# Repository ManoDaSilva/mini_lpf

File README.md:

# Mini LPF: an HF low pass filter kit

A small low pass filter (LPF) for QRP transmitters on the HF amateur bands, from 80m to 10m. It has SMA connectors on both ends and three hand-wound toroidal inductors.

This is an entry-level project. The aim is to learn how a low pass filter works and how to design and wind a toroidal inductor. You choose your band, wind three coils and solder four capacitors. The result is a working harmonic filter you can put after any small transmitter, such as an Si5351 beacon or a QRP PA.

## Context

The kit was designed for a YOTA (Youngsters On The Air) sub-regional event, with 30 kits to build in a workshop. YOTA is the youth programme of IARU Region 1 ([ham-yota.com](https://www.ham-yota.com/), [IARU R1 Youth](https://www.iaru-r1.org/about-us/committees-and-working-groups/youth/)).

The design goals for the event were:

- Low cost: under 2 EUR per participant if possible.
- Few different parts: one core type and one wire size for every band.
- SMA input and output, on a custom PCB.
- A choice of band for each participant: 80m, 40m, 20m, 15m or 10m.

The design is not limited to the event. Anyone who needs a small harmonic filter or wants to learn about filters can use it. The table below covers all HF bands from 80m to 10m.

## Repository content

| Folder | Content |
|---|---|
| `mini_lpf_pcb/` | KiCad project: schematic, PCB and footprints |
| `docs/` | Source documentation, including the original G-QRP filter article (`gqrplpf.pdf`) |

## Working principle

A transmitter does not only put out its wanted frequency. It also puts out harmonics: signals at 2, 3, 4 or more times that frequency. A square-wave source, such as an Si5351 or a switching PA, is rich in odd harmonics. These harmonics can cause interference on other bands, and radio rules require them to be kept low.

A low pass filter lets frequencies below its cutoff pass with little loss and attenuates frequencies above it. This filter is a 7-element Chebyshev design by Ed Wetherhold, W3NQN. George Dobbs, G3RJV, published a practical version for the G-QRP Club (see `docs/gqrplpf.pdf`). It uses standard capacitor values, which makes it easy to build.

```
IN o----+---L1---+---L2---+---L3---+----o OUT
        |        |        |        |
        C1       C2       C3       C4
        |        |        |        |
       GND      GND      GND      GND
```

The filter has 50 ohm input and output impedance and is symmetrical, so IN and OUT can be swapped.

Component numbering in this repo follows the signal path: C1, L1, C2, L2, C3, L3, C4. The G-QRP article numbers the parts 1 to 7 along the ladder. The mapping is:

| This repo | G-QRP article |
|---|---|
| C1, C4 | C1, C7 |
| C2, C3 | C3, C5 |
| L1, L3 | L2, L6 |
| L2 | L4 |

## Band values (80m to 10m)

All coils are wound on a T37-6 (yellow) core. Capacitor values are in pF. Inductance values come from Table 1 of the G-QRP article, except 60m, which comes from the QRP Labs LPF kit (the G-QRP article has no 60m filter).

| Band | Cutoff F-co (MHz) | -3 dB (MHz) | C1, C4 (pF) | C2, C3 (pF) | L1, L3 (µH) | L1, L3 turns | L2 (µH) | L2 turns |
|---|---|---|---|---|---|---|---|---|
| 80m | 4.125 | 5.11 | 470 | 1200 | 2.434 | 28 | 3.012 | 32 |
| 60m | | | 680 | 1200 | 2.12 | 27 | 2.30 | 28 |
| 40m | 7.36 | 9.04 | 270 | 680 | 1.380 | 21 | 1.698 | 24 |
| 30m | 10.37 | 11.62 | 270 | 560 | 1.090 | 19 | 1.257 | 20 |
| 20m | 14.40 | 16.41 | 180 | 390 | 0.773 | 16 | 0.904 | 17 |
| 17m | 18.93 | 22.89 | 110 | 270 | 0.548 | 13 | 0.668 | 15 |
| 15m | 21.55 | 27.62 | 82 | 220 | 0.444 | 12 | 0.561 | 14 |
| 12m | 25.24 | 28.94 | 100 | 220 | 0.438 | 12 | 0.515 | 13 |
| 10m | 31.66 | 40.52 | 56 | 150 | 0.303 | 10 | 0.382 | 11 |

Notes on the table:

- The G-QRP article winds 80m on a T37-2 (red) core with 25 and 27 turns. This repo uses T37-6 on every band so that the kit needs only one core type. On T37-6, 80m needs 28 and 32 turns.
- For 40m, Table 4 of the G-QRP article lists 19 and 21 turns on T37-6. The turns formula with the Table 1 inductances gives 21 and 24 turns. The QRP Labs kit also uses 21 and 24 turns on T37-6 for 40m. This repo uses 21 and 24.
- For 17m, the G-QRP value for C1 and C4 is 110 pF. QRP Labs uses 100 pF because 110 pF is hard to find. 100 pF and 10 pF in parallel give 110 pF.
- For 80m and 60m, 1200 pF can be made from 1000 pF and 220 pF in parallel (1220 pF), or 680 pF and 470 pF (1150 pF).

## Designing a coil yourself

The number of turns comes from the inductance and the core's AL value:

```
N = 10 x sqrt(L / L10)
```

- N is the number of turns.
- L is the inductance you need, in µH.
- L10 is the inductance of the core with 10 turns, in µH. For a T37-6 it is 0.30 µH. For a T37-2 it is 0.40 µH.

Example for the 20m L1: N = 10 x sqrt(0.773 / 0.30) = 16.05, so 16 turns.

Round to the nearest whole number of turns. The AL value of the core has a tolerance of about 5%, so the result does not need to be more precise than that.

The same formula works with the AL value given in nH per turn squared: N = sqrt(L / AL). For a T37-6, AL is 3.0 nH/turn².

## Recommended components

| Qty | Part | Notes |
|---|---|---|
| 3 | T37-6 iron powder toroid (yellow) | Micrometals or Amidon. Unbranded cores may use a different mix. Measure a sample before you buy many. |
| 1.5 m | Enamelled copper wire, 0.35 to 0.4 mm (AWG 27 to 26) | Use solderable (polyurethane) enamel, which strips with a hot soldering iron. |
| 4 to 8 | Ceramic disc capacitors, C0G / NP0 | Values from the table. 5.08 mm lead spacing. 50 V or more, 100 V if you use more than 5 W. |
| 2 | SMA female, edge-mount | Made for a 1.6 mm board. Check the footprint against the exact part you buy. |
| 1 | PCB from `mini_lpf_pcb/` | 2 layers, 1.6 mm FR4 |

Why T37-6: Micrometals mix 6 is made for about 3 to 40 MHz, which covers all bands from 80m to 10m. The G-QRP article (Table 3) rates the T37-6 for up to 25 W.

Why 0.4 mm wire: the hardest coil is the 80m L2 with 32 turns. With enamel, 0.4 mm wire is about 0.45 mm thick. 32 turns take about 14.4 mm of the 15 mm available at the inner edge of the core. It fits in one layer, but only just. 0.35 mm wire leaves more room. On the higher bands the wire size does not matter, because the coils have far fewer turns.

### About capacitors

C0G (also sold as NP0) capacitors are the right choice. Their value stays stable with temperature and voltage, and their RF loss is low.

Generic ceramic discs without a temperature rating can work, with some care:

- Avoid Z5U and Y5V types. Their value can drop by half when cold, which moves the cutoff up so far that the 2nd harmonic is barely attenuated.
- Y5P and X7R types are acceptable. They add about 0.5 dB of loss, which does not matter at QRP power.
- Buy each value from one batch. When all capacitors are off in the same direction, the filter stays matched. When some are high and some are low, the match gets poor (return loss of 5 to 8 dB).
- Small values (100 pF and below) are usually class 1 ceramics anyway, even when sold as generic.
- If you can, measure a few capacitors of each batch with a component tester.

## Winding the toroids

- Each time the wire passes through the centre of the core counts as one turn. Count the turns on the inside of the core.
- Cut the wire first. A coil needs about 1.3 cm of wire per turn on a T37, plus about 7 cm for the leads and a margin. Example: 32 turns x 1.3 cm + 7 cm = 49 cm.
- For long coils, start in the middle of the wire. Thread the core onto the wire so the first turn sits at the middle. Wind half the turns with one end, then turn the core over and wind the rest with the other end, going on in the same direction around the core. You only pull half the wire through each time. This trick comes from the QRP Labs instructions.
- Pull each turn tight against the core. Loose turns change the inductance and move around later.
- Spread the turns evenly over about three quarters of the core. Leave a gap between the start and the end of the winding. If the two ends are too close, they add capacitance.
- For the 80m coils, wind the turns touching each other on the inner edge from the start. Otherwise the last turns will not fit in one layer. If a few turns end up on top of the others, the coil still works.
- To fine-tune: pushing the turns closer together raises the inductance a little, and spreading them lowers it.
- Strip and tin the leads. Solderable enamel melts at about 380 to 400 °C. Hold the lead in a blob of solder on the iron until it is shiny and tinned. With other enamel, scrape it off with a blade or fine sandpaper. A lead that is not tinned all round makes a bad joint, which is the most common fault in this kit.
- Tin the leads up to about 2 mm from the core, so no bare enamel sits in the solder joint.
- On the PCB the core stands upright. A dot of hot glue or nail varnish under the core keeps it from moving.

If you have an LC meter or a NanoVNA, measure each coil before you solder it in.

## Building

1. Solder the two SMA connectors first. They are the largest parts and the board must sit flat between their legs.
2. Solder the four capacitors. Keep their leads short and the body close to the board.
3. Wind and solder L1, L2 and L3. Check the turn count for your band twice before soldering.
4. Write your callsign and band in the box on the board.

## Testing

With a NanoVNA, or another vector network analyser:

1. Calibrate with the cables you will use, including a through connection.
2. Connect the filter between port 1 and port 2.
3. Sweep from 1 MHz to about 4 times your band.
4. Check the insertion loss (S21) in your band. Expect less than 0.5 dB with C0G capacitors.
5. Check the return loss (S11) in your band. 15 dB or better is good.
6. Check the attenuation at 2 and 3 times your band frequency.

Typical simulated values with C0G capacitors and the turn counts in the table: about 0.2 dB loss in band, about 20 dB return loss or better, and about 55 dB attenuation at the 3rd harmonic on 80m and 10m.

Without a VNA, you can check the SWR of the filter into a 50 ohm dummy load with your transmitter. A good filter shows a low SWR on its band. A coil with the wrong number of turns usually shows up as a high SWR.

## Using the filter

Put the filter between the transmitter output and the antenna. If you use an amplifier, the filter goes after the amplifier. A filter before a switching PA does not help, because the PA creates harmonics again.

An Si5351 alone gives about 10 mW into 50 ohms. With this filter, that is enough for a WSPR beacon. K6HX reports spots at more than 900 km on 20m with about 10 mW and a G3RJV filter on T37-6 cores ([K6HX blog](https://brainwagon.org/blog/post-field-day-report-on-k6hx-beacon-operations/)).

The filter is designed for QRP power, up to 10 W as in the G-QRP article.

Transmitting on the amateur bands requires a licence. For tests and demonstrations without a licensed operator, transmit into a 50 ohm dummy load.

## Sources

- George Dobbs, G3RJV, "A Short Guide to Harmonic Filters for QRP Transmitter Output", G-QRP Club Technical Page 2, 2009. Based on the W3NQN articles in Short Wave Magazine, December 1983 and January 1984. Archived page: [web.archive.org](https://web.archive.org/web/20100124053352/http://www.gqrp.com/technical2.htm). Copy in this repo: `docs/gqrplpf.pdf`.
- QRP Labs, Low Pass Filter kit: [kit page](https://www.qrp-labs.com/lpfkit), [assembly instructions](https://www.qrp-labs.com/images/lpfkit/instructions2a.pdf), [60m values](https://www.qrp-labs.com/images/lpfkit/instructions2.pdf), [toroid evaluation](https://www.qrp-labs.com/images/lpfkit/toroid.pdf).
- Micrometals RF toroid data (dimensions and AL values): [table](https://cx1ddr.myqnapcloud.com/toroide/mtoroids.htm).
- Electronic Design, "Designing Extended-Range Toroidal Inductors" (T37-6 between 3 and 40 MHz): [article](https://www.electronicdesign.com/technologies/components/article/21773038/designing-extended-range-toroidal-inductors).
- SOTABEAMS, low pass filter designs (loss with inductor Q of 140): [PDF](https://www.sotabeams.co.uk/content/LPF-DESIGNS.pdf).
- Mark VandeWettering, K6HX, beacon report: [blog](https://brainwagon.org/blog/post-field-day-report-on-k6hx-beacon-operations/).
- YOTA: [ham-yota.com](https://www.ham-yota.com/).

## Licence

This project is free hardware and documentation: you can redistribute it and/or modify it under the terms of the GNU General Public License as published by the Free Software Foundation, version 3 of the License, or (at your option) any later version. See [LICENSE](LICENSE).

This project is distributed in the hope that it will be useful, but WITHOUT ANY WARRANTY; without even the implied warranty of MERCHANTABILITY or FITNESS FOR A PARTICULAR PURPOSE. See the GNU General Public License for more details.

Exception: `docs/gqrplpf.pdf` is © 2009 GQRP Club. It is included as a reference and is not covered by the GPL.

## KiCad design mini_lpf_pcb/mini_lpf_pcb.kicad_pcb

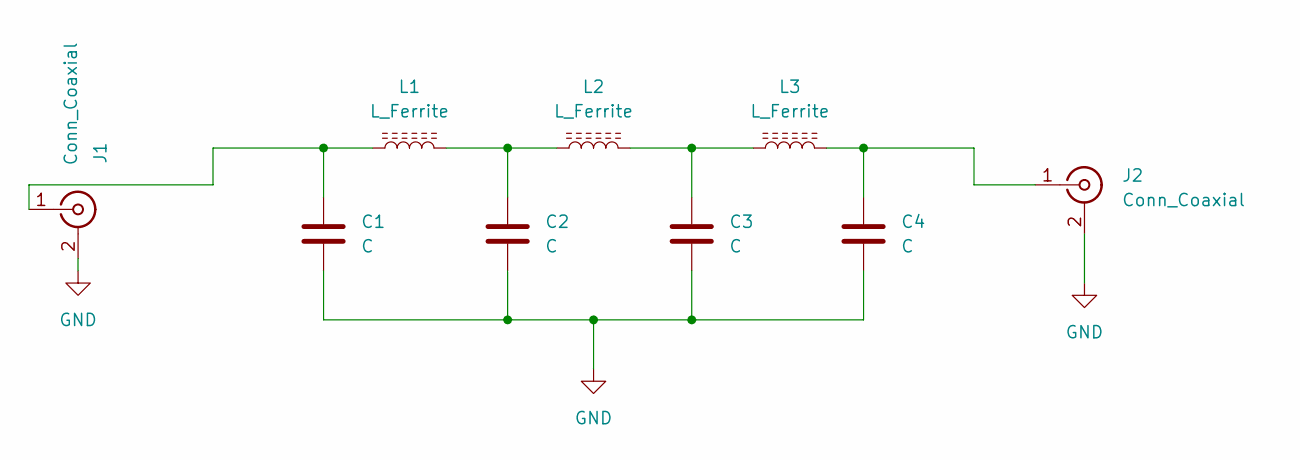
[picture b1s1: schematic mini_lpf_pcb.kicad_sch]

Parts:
C1, C2, C3, C4: C; C_Disc_D5.0mm_W2.5mm_P5.00mm
J1, J2: Conn_Coaxial; SMA_Samtec_SMA-J-P-H-ST-EM1_EdgeMount
L1, L2, L3: L_Ferrite; T37_vertical

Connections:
GND: C1.2, C2.2, C3.2, C4.2, J1.2 (Ext), J2.2 (Ext)
unnamed: C2.1, L1.2, L2.1
unnamed: C3.1, L2.2, L3.1
unnamed: C1.1, J1.1 (In), L1.1
unnamed: C4.1, J2.1 (In), L3.2

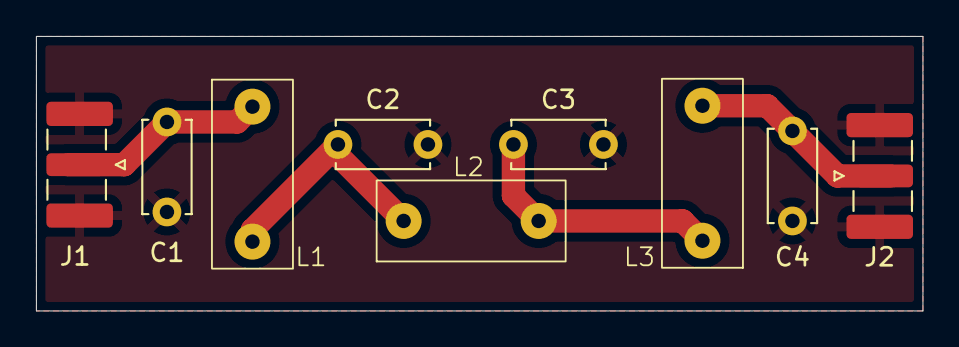
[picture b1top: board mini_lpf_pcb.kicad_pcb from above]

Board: 2 copper layers, 49.2 x 15.2 mm, 9 parts (0 on the bottom side), 5 nets.
